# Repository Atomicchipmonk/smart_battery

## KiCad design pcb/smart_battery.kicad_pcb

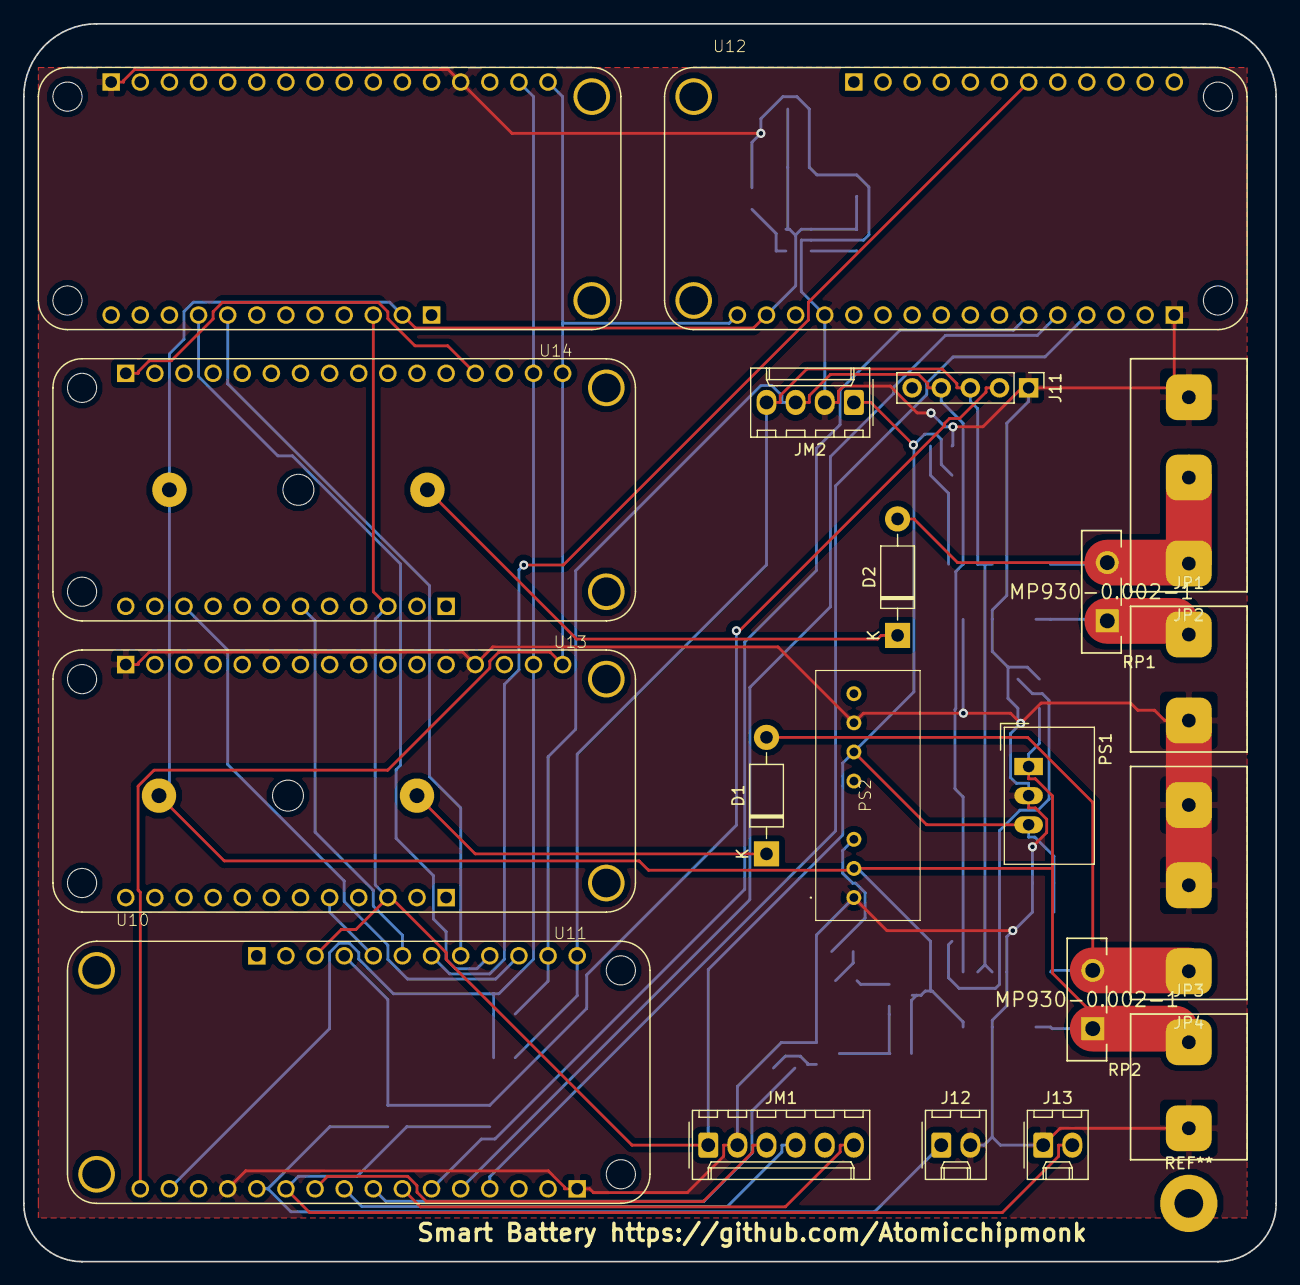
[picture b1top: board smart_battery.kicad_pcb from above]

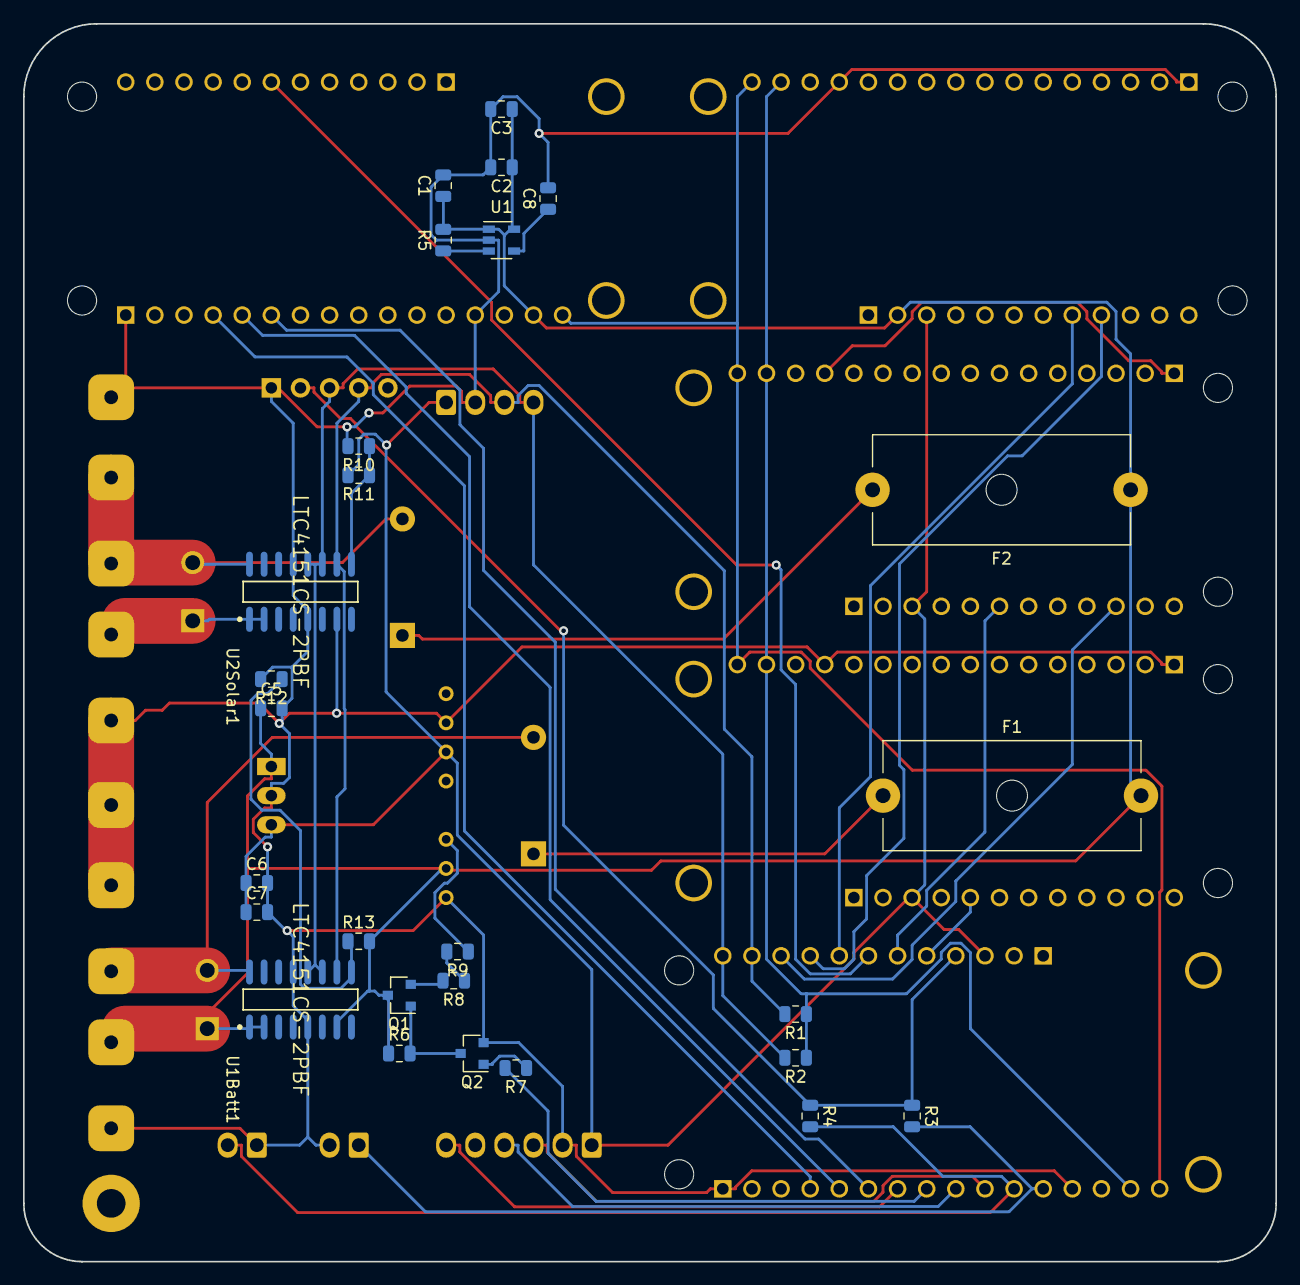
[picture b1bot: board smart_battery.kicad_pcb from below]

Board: 2 copper layers, 109.2 x 108.0 mm, 47 parts (27 on the bottom side), 38 nets.

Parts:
C1, C2, C5, C6, C7: C10uF; C_0805_2012Metric
C3: C1uF; C_0805_2012Metric
C8: C10nF; C_0805_2012Metric
D1: 1N4002; D_DO-41_SOD81_P10.16mm_Horizontal
D2: 1N4001; D_DO-41_SOD81_P10.16mm_Horizontal
F1, F2: Fuse_Small; Fuseholder_Cylinder-5x20mm_Schurter_0031_8201_Horizontal_Op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
J11: Conn_01x05_RTC; PinHeader_1x05_P2.54mm_Vertical
J12: Conn_HtrTh; Molex_KK-254_AE-6410-02A_1x02_P2.54mm_Vertical
J13: Conn_BattTh; Molex_KK-254_AE-6410-02A_1x02_P2.54mm_Vertical
JM1: RockBLOCK Modem; Molex_KK-254_AE-6410-06A_1x06_P2.54mm_Vertical
JM2: I2C Connector; Molex_KK-254_AE-6410-04A_1x04_P2.54mm_Vertical
JP1: SolarIn; 7.5mm_screw_conn_1x2
JP2: SolarOut; 7.5mm_screw_conn_1x3
JP3: BatteryIn; 7.5mm_screw_conn_1x2
JP4: BatteryOut; 7.5mm_screw_conn_1x3
PS1: TSR_1-2450; Converter_DCDC_TRACO_TSR-1_THT
PS2: TEC_2-2411; TEC24811
Q1, Q2: MMBT5551L; SOT-23
R1, R2: R2k; R_0805_2012Metric
R3, R4: R10k; R_0805_2012Metric
R5: 100K; R_0805_2012Metric
R6: R68k; R_0805_2012Metric
R7: 5.1K; R_0805_2012Metric
R8: 15K; R_0805_2012Metric
R9: 1K; R_0805_2012Metric
R10, R12: 3.3K; R_0805_2012Metric
R11, R13: R6.8k; R_0805_2012Metric
RP1, RP2: MP930-0.002-1; Caddock-MP930-0-0-Recommended_Land_Pattern_
U1: SPX3819M5-L-3-3; SOT-23-5
U1Batt1, U2Solar1: LTC4151CS-2PBF; Linear_Technology-LTC4151CS-2PBF-Level_B
U10: FEATHER_M0_ADALOGGER; MODULE_FEATHER_M0_BASIC_PROTO
U11: FEATHERWING_HEATER_RELAY; MODULE_FEATHER_POWER_RELAY
U12: FEATHERWING_ETHERNET; MODULE_FEATHER_ETHERNET_MODULE
U13, U14: FEATHERWING_MINI_RELAY; MODULE_FEATHER_MINI_RELAY

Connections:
+3V3: R1.1, R2.1, U10.P1_15, U11.P1_15, U13.P1_15, U14.P1_15
+5V: C6.1, C7.1, JM1.1, JM2.1, PS1.3, PS2.6, R11.2, U10.P2_3, U11.P2_3, U13.P2_3, U14.P2_3
+24V: JP1.1, RP1.1, U2Solar1.1, U2Solar1.2
+48V: C1.1, C2.1, C3.1, C5.1, F1.2, F2.1, JP3.1, PS1.1, PS2.2, Q1.3, R5.2, R6.1, R13.2, RP2.1, U1.1, U1.5, U1Batt1.1, U1Batt1.2, U1Batt1.7, U12.P1_15, U14.P2_2
/48VEN: R7.2, U10.P1_8
/ENCS: U10.P2_7, U12.P2_7
/HTEN: U10.P2_5, U11.P2_5
/MISO: U10.P1_4, U12.P1_4
/MOSI: U10.P1_5, U12.P1_5
/PSET: U10.P2_9, U14.P2_9
/PUSET: U10.P2_8, U14.P2_8
/RBEN: JM1.6, U10.P1_7
/RBRX: JM1.3, U10.P1_10
/RBTX: JM1.4, U10.P1_9
/SCK: U10.P1_6, U12.P1_6
/SCL: J11.4, JM2.3, R1.2, U1Batt1.10, U2Solar1.10, U10.P2_11
/SDA: J11.3, JM2.4, R2.2, U1Batt1.11, U1Batt1.12, U2Solar1.11, U2Solar1.12, U10.P2_12
/SSET: U10.P2_6, U13.P2_6
/SUSET: U10.P2_10, U13.P2_10
/THBAT: J13.2, R4.2, U10.P1_11
/THHTR: J12.1, R3.2, U10.P1_12
/VPIN: J11.2, R3.1, R4.1, U10.P2_4
/~RST: U10.P1_16, U11.P1_16, U12.P1_16, U13.P1_16, U14.P1_16
GND: C1.2, C2.2, C3.2, C5.2, C6.2, C7.2, C8.2, J11.1, J12.2, J13.1, JM1.2, JM2.2, JP1.2, JP2.3, JP3.2, JP4.2, JP4.3, PS1.2, PS2.1, PS2.7, Q2.2, R10.2, R12.2, U1.2, U1Batt1.5, U1Batt1.13, U2Solar1.5, U2Solar1.7, U2Solar1.13, U10.P1_1, U10.P1_13, U11.P1_1, U11.P1_13, U12.P1_1, U12.P1_13, U14.P1_1, U14.P1_13
unnamed: C8.1, U1.4
unnamed: D1.1, F1.1
unnamed: D1.2, JP4.1, RP2.2, U1Batt1.16
unnamed: D2.1, F2.2
unnamed: D2.2, JP2.1, JP2.2, RP1.2, U2Solar1.16
unnamed: PS2.3, R9.1
unnamed: Q1.1, Q2.3, R6.2
unnamed: Q1.2, R8.2
unnamed: Q2.1, R7.1
unnamed: R5.1, U1.3
unnamed: R8.1, R9.2
unnamed: R10.1, R11.1, U2Solar1.9
unnamed: R12.1, R13.1, U1Batt1.9
unnamed: U13.P1_1, U13.P1_13

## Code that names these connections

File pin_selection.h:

//Blink LED
#define BLINK_LED 8

//Thermistor pins
#define THERMISTOR_PIN_HEATER A0        //THHTR
#define THERMISTOR_PIN_BATTERY A1       //THBAT

//Iridium Pins
#define ROCKBLOX_IRIDIUM_RX A2          //RBRX
#define ROCKBLOX_IRIDUIM_TX A3          //RBTX

//Power Enable Pins
#define PWR_48V_ENABLE_PIN A4           //48VEN
#define PWR_ROCKBLOX_ENABLE_PIN A5      //RBEN

//Power sense address
#define CURRENT_SENSE_SOLAR_ADDR 0xFE
#define CURRENT_SENSE_BATTERY_ADDR 0xFF
#define VOLTAGE_SENSE_SOLAR_ADDR 0xFE
#define VOLTAGE_SENSE_BATTERY_ADDR 0xFF


//3.3v enable rail
#define VPIN 13                         //VPIN

//Digital output
#define HEATER_RELAY_PIN 12             //HTEN
#define CHARGE_RELAY_ON_PIN 11          //SSET
#define OUTPUT_RELAY_OFF_PIN 9          //PUSET
#define OUTPUT_RELAY_ON_PIN 6           //PSET
#define CHARGE_RELAY_OFF_PIN 5          //SUSET

//IP ADDRESSES
#define ETHERNET_CHIP_SELECT 10         //ENCS
#define BATTERY_IP_ADDRESS 169.254.2.55
#define INFLUX_DB_IP_ADDRESS granolamatt.duckdns.org:1210

//SD Card
#define SD_CHIP_SELECT 4                //internal
#define SD_CARD_INSERTED 7              //internal

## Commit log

2020-12-06 first init of battery functions - includes relay control, basic serial and sd card logging
2020-12-08 added sleep capability, updated pin selection, added 20 second timer for reboot. debug.h define sets if serial is used or not, along with if entire system is put to sleep inbetween logs
2020-12-15 updates for printing and logic. printing floats does not work
2021-01-18 first move to m0, not working yet
2021-01-19 holding commit to get code working on m0 from previous 32u4
2021-01-19 working rotating logs on SD card. Includes relay functions and rtc
2021-01-19 an unceremonious rewrite of the battery software. includes working sd logic, rtc and relay functions
2021-01-23 Initial push, template only
2021-01-24 working logger for serial, ethernet and sd card going to influx db with NTP timing
2021-01-24 Laying out the schematic
2021-01-25 some software cleanup and hopefully the final pinout for relays, rtc and ethernet
2021-01-28 Added thermistors and RTC. Most feather pinouts done
2021-02-01 Added 3.3 volt ethernet circuit
2021-02-05 Added connectors and start the PCB
2021-02-05 Organizing trying to pull in libraries
2021-02-05 Moved symbol libraries into git
2021-02-06 Placed resistor and capacitor pads
2021-02-06 Added switches to power battery module from large battery
2021-02-06 Added rockblock modem connection
2021-02-06 Added i2c connector
2021-02-06 Added connector symbols
2021-02-06 Corrected relay pins to match main board
2021-02-07 Moving to a feather symbol library
2021-02-07 Moved all feather components to symbols
2021-02-07 Added footprints for relays and ethernet
2021-02-07 Added ide pin names to symbol
2021-02-07 Post review changes
2021-02-08 added pin 13 enable for rtc and thermistors
2021-02-09 Laying out board
2021-02-09 First board layout done
2021-02-10 Made gerber files and changed grounds
2021-02-10 Added mounting holes and Smart Battery label
2021-02-12 Added diodes to protect battery inputs
2021-02-15 Fixed Sean comments, still need to redo the PCB
2021-02-19 Added power symbols instead of labels for power buses
2021-02-20 Routed the new layout just need ground plane
2021-02-20 Made the ground plane
2021-02-20 Plotted the gerber file
2021-03-07 Fixed board issues with pads
2021-03-13 updated pins, weekend test ongoing without debug. Added information about SD card availability and connectivity
2021-03-15 added config capability through files to set your batteries ID
2021-03-16 Added ethernet availability logic and overall battery state machine logic in comments
2021-04-04 Added a few more psuedo code comments for overall logic
2021-04-28 LTC4151 code for voltage reading
2021-05-04 halfway through an SD card update
2021-05-11 added config system to read in ip, mac, server name and battery name config files. compiles, needs to be tested
2021-05-15 got configuration mainly working, debugging possible client issue
2021-05-15 Added significant amount of battery state logic and checks, compiles, runs, needs to be significantly checked
2021-05-15 Fixed serial required boot bug, added 48v enable so it can run on battery
2021-05-15 working battery systemgit add *! Safe mode tested with hair dryer
2021-06-24 added battery percentage calculation
